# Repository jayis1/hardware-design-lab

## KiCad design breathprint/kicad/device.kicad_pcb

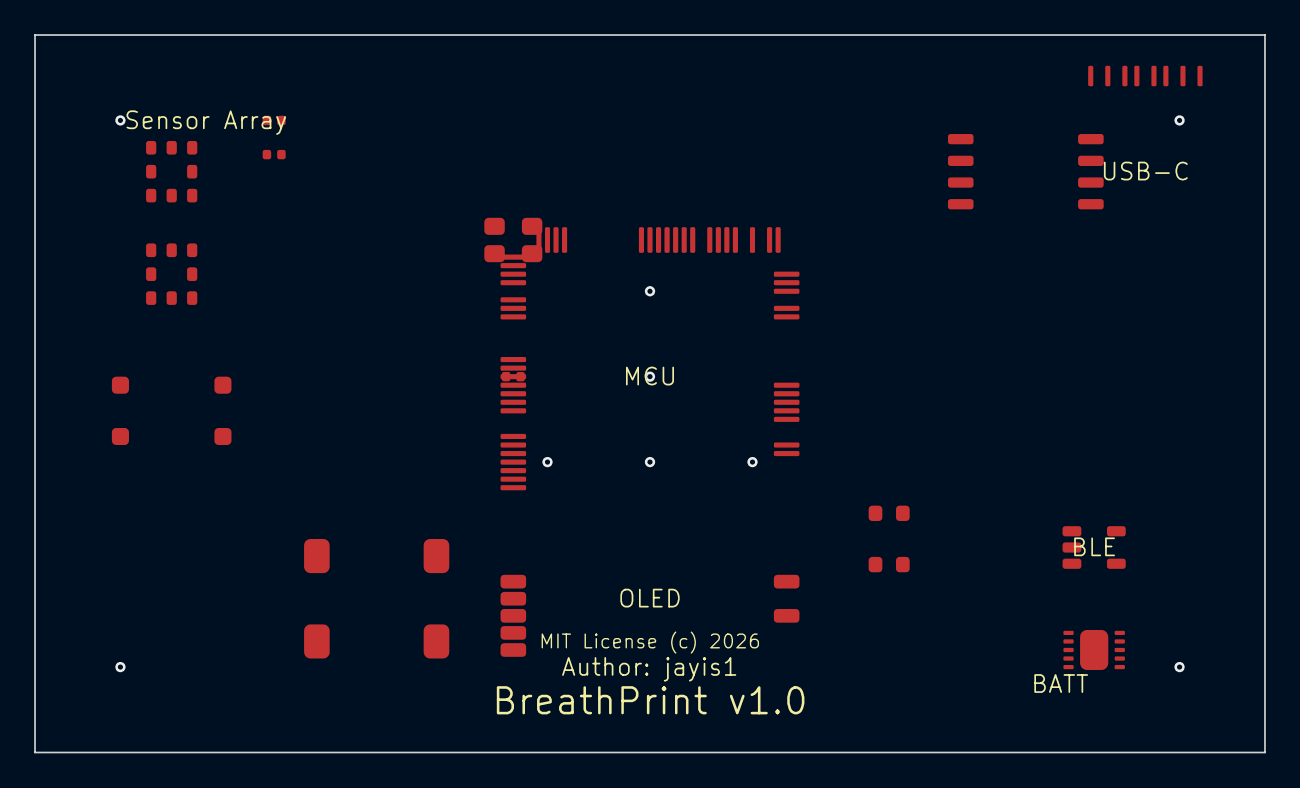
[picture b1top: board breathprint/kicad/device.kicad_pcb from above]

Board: 4 copper layers, 72.0 x 42.0 mm, 16 parts (0 on the bottom side), 23 nets, no tracks yet.

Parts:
C1: 100nF; C_0402_1005Metric
D1: Status_LED; LED_0603_1608Metric
D2: Sample_LED; LED_0603_1608Metric
J1: USB-C; USB_C_Receptacle_GCT_USB4085
R1, R2: 4.7k; R_0402_1005Metric
SW1: Analyze_BTN; SW_Push_1P1T_NO_6x6mm_H9.5mm
U1: STM32H733VGT6; LQFP-100_14x14mm_P0.5mm
U2, U3: BME688; Bosch_LCC-8_3.6x4.2mm_P1.2mm
U4: SCD41; Sensirion_SCD41
U5: W25Q64JVSIQ; SOIC-8_5.27x5.27mm_P1.27mm
U6: MCP73831T-2ACI; SOT-23-5
U7: TPS63031DSKR; VSON-10-1EP_3x3mm_P0.5mm_EP1.65x2.35mm
U8: SSD1306_128x64; SSD1306_0.96in_128x64
Y1: 16MHz; Crystal_SMD_3225-4Pin_3.2x2.5mm

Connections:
BTN_ANALYZE: SW1.1, SW1.3, U1.23
CHRG_STAT: U1.77, U6.1
DISP_CS: U1.51, U8.3
DISP_DC: U1.57, U8.4
DISP_RST: U1.56, U8.5
FLASH_CS: U1.3, U5.1
GND: C1.2, D1.2, D2.2, J1.A1, J1.B1, SW1.2, SW1.4, U1.10, U1.21, U1.27, U1.49, U1.74, U1.99, U2.2, U2.6, U2.7, U3.2, U3.7, U4.2, U5.4, U6.2, U6.5, U7.3, U7.4, U7.7, U7.8, U7.11, U8.2, Y1.2, Y1.4
HSE_IN: U1.12, Y1.1
HSE_OUT: U1.13, Y1.3
I2C1_SCL: R1.2, U1.92, U2.4, U3.4, U4.3
I2C1_SDA: R2.2, U1.93, U2.5, U3.5, U4.4
SAMPLE_LED: D2.1, U1.47
SPI2_MOSI: U1.54, U8.7
SPI2_SCK: U1.52, U8.6
SPI4_MISO: U1.4, U5.2
SPI4_MOSI: U1.1, U5.5
SPI4_SCK: U1.5, U5.6
STATUS_LED: D1.1, U1.46
USB_DM: J1.A7, U1.44
USB_DP: J1.A6, U1.45
VBAT: U1.6, U6.3, U7.1, U7.2
VCC: C1.1, R1.1, R2.1, U1.11, U1.22, U1.28, U1.50, U1.75, U1.100, U2.1, U2.3, U2.8, U3.1, U3.3, U3.6, U3.8, U4.1, U5.3, U5.7, U5.8, U7.5, U7.6, U7.9, U7.10, U8.1
VUSB: J1.A4, J1.B4, U6.4

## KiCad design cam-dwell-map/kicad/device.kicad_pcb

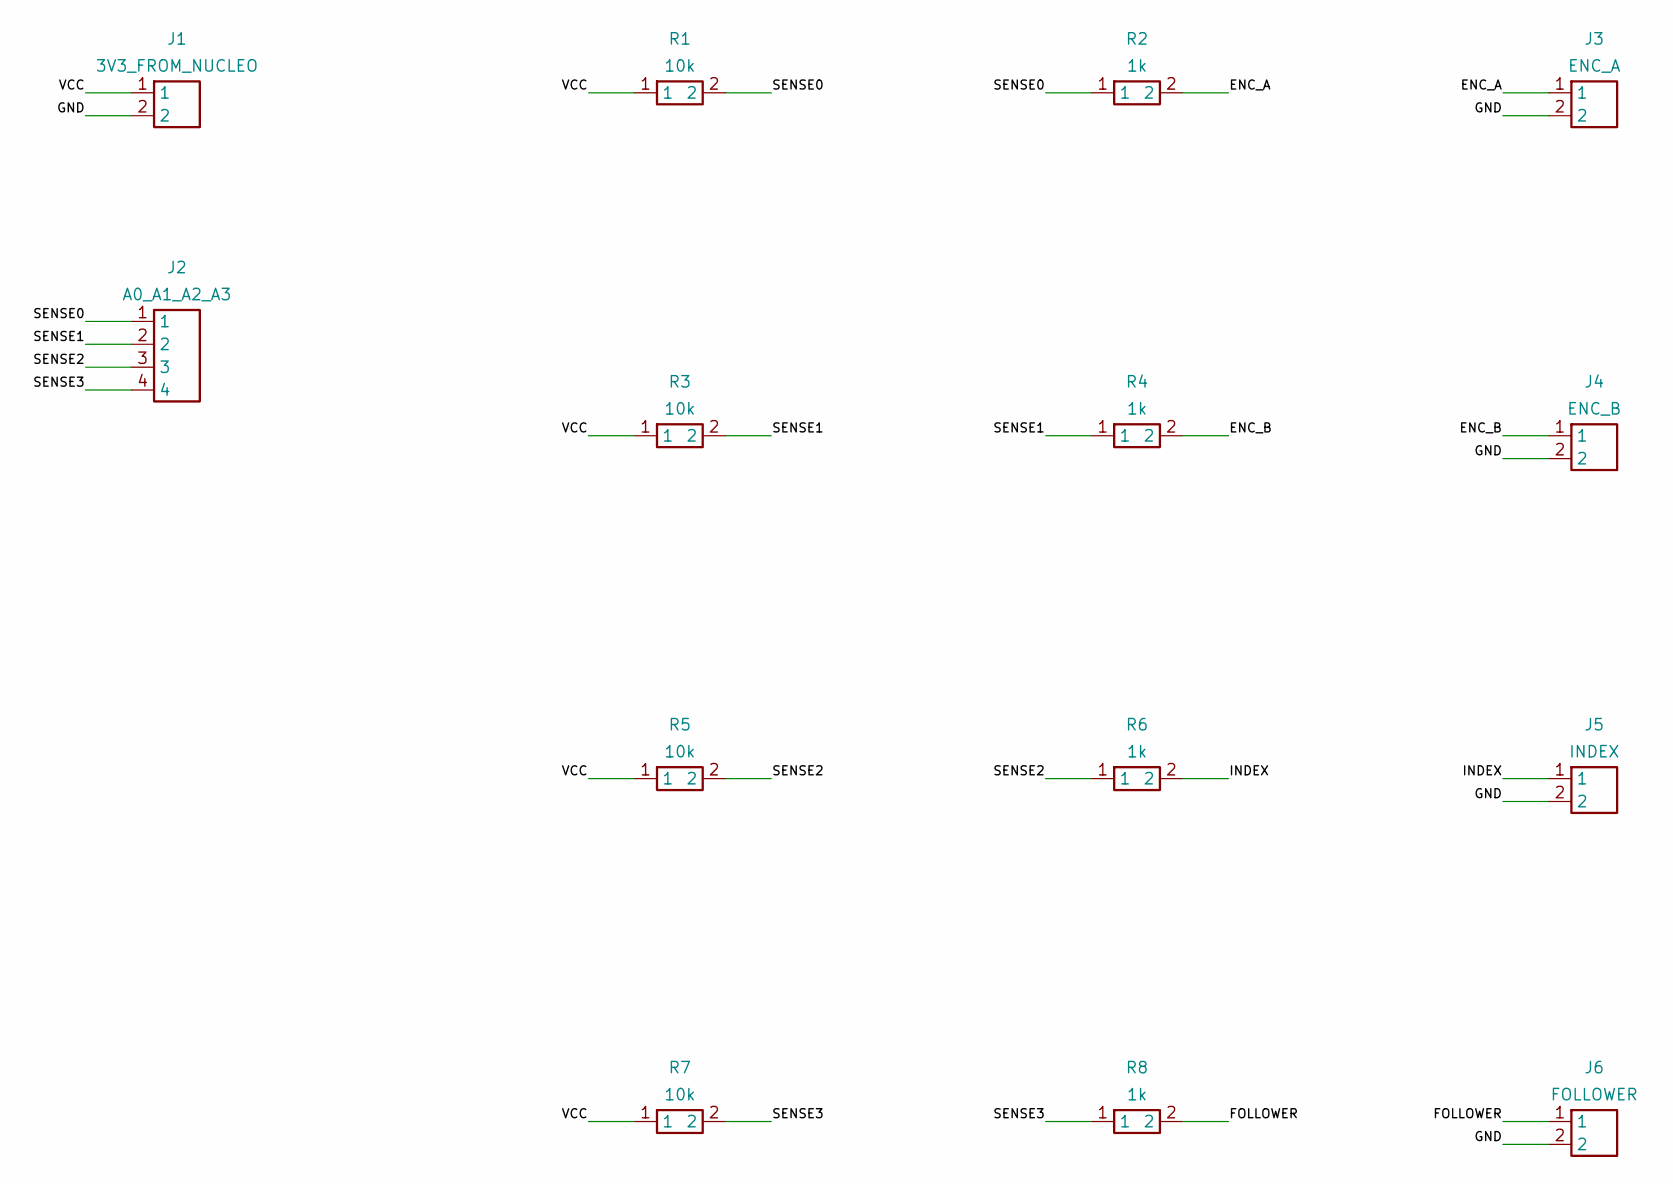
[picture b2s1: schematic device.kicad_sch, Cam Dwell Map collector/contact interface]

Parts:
J1: 3V3_FROM_NUCLEO; PinHeader_1x02_P2.54mm_Vertical
J2: A0_A1_A2_A3; PinHeader_1x04_P2.54mm_Vertical
J3: ENC_A; PinHeader_1x02_P2.54mm_Vertical
J4: ENC_B; PinHeader_1x02_P2.54mm_Vertical
J5: INDEX; PinHeader_1x02_P2.54mm_Vertical
J6: FOLLOWER; PinHeader_1x02_P2.54mm_Vertical
R1, R3, R5, R7: 10k; R_Axial_DIN0207_L6.3mm_D2.5mm_P7.62mm_Horizontal
R2, R4, R6, R8: 1k; R_Axial_DIN0207_L6.3mm_D2.5mm_P7.62mm_Horizontal

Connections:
ENC_A: J3.1, R2.2
ENC_B: J4.1, R4.2
FOLLOWER: J6.1, R8.2
GND: J1.2, J3.2, J4.2, J5.2, J6.2
INDEX: J5.1, R6.2
SENSE0: J2.1, R1.2, R2.1
SENSE1: J2.2, R3.2, R4.1
SENSE2: J2.3, R5.2, R6.1
SENSE3: J2.4, R7.2, R8.1
VCC: J1.1, R1.1, R3.1, R5.1, R7.1

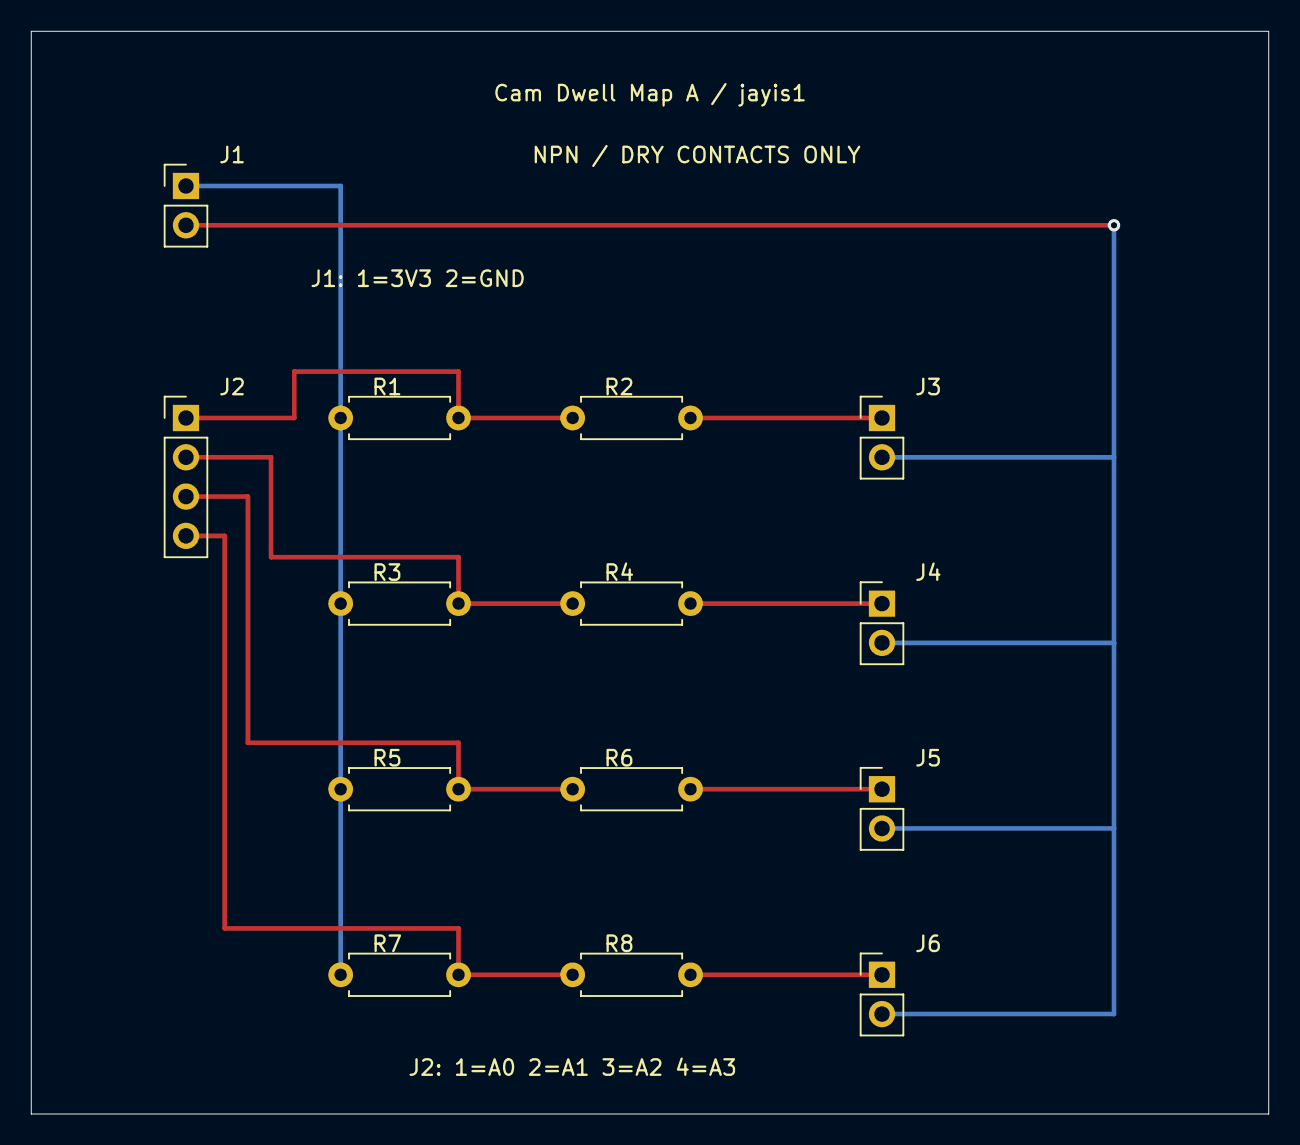
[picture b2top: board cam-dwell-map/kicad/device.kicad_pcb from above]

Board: 2 copper layers, 80.0 x 70.0 mm, 14 parts (0 on the bottom side), 10 nets.

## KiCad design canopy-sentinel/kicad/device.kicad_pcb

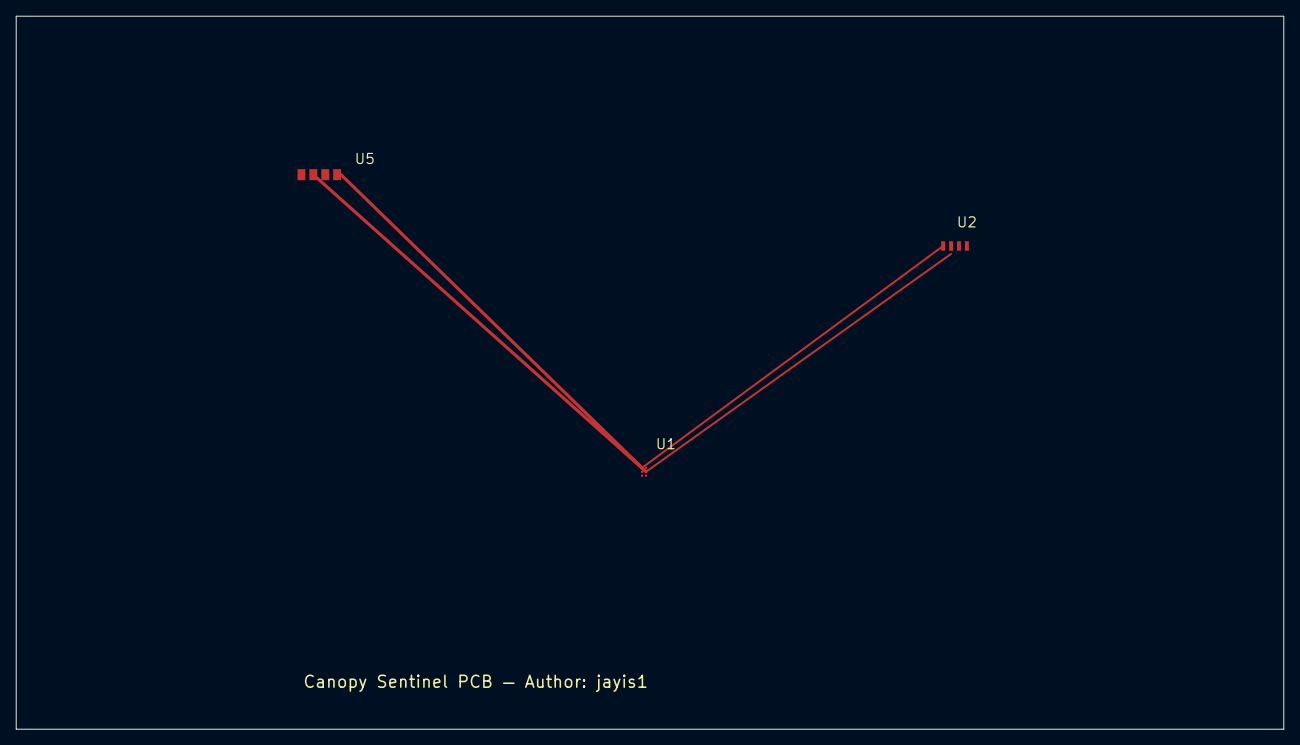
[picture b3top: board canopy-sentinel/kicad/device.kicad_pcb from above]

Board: 2 copper layers, 160.0 x 90.0 mm, 3 parts (0 on the bottom side), 4 nets.

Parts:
U1: STM32U585AII6; TFBGA-169_7x7mm_Layout13x13_P0.5mm
U2: MLX90640; LGA-32_8x8mm_P0.8mm
U5: ESP32-S3-WROOM-1

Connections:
3V3: U1.A1, U2.1, U5.1
GND: U1.A2, U2.4, U5.2
I2C1_SCL: U1.B1, U2.2
I2C1_SDA: U1.B2, U2.3

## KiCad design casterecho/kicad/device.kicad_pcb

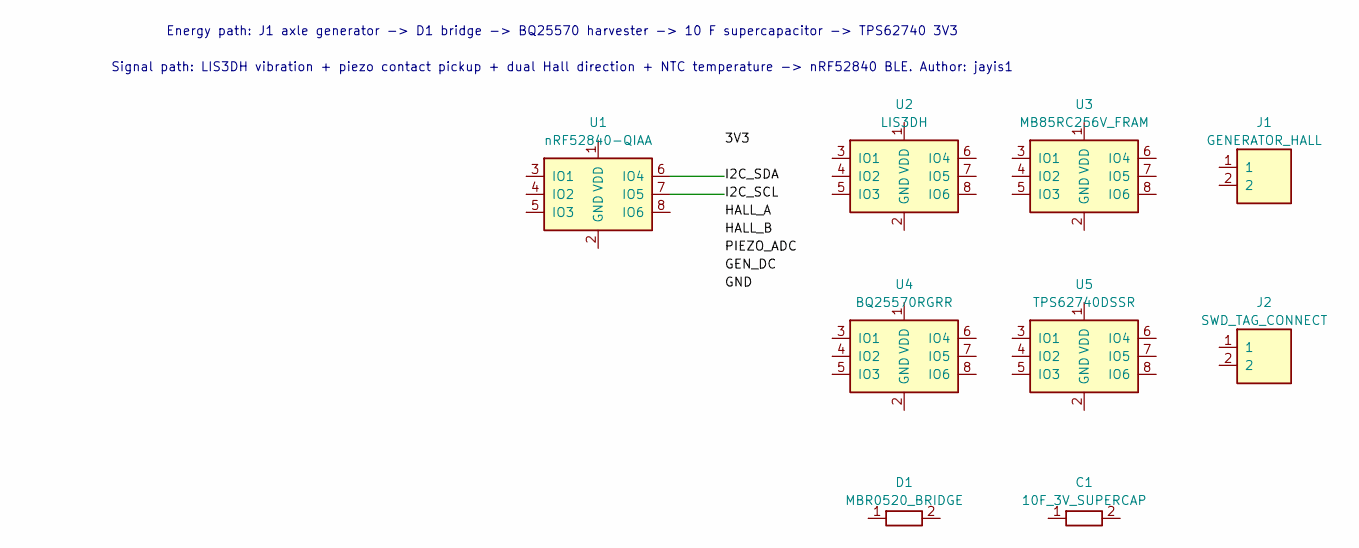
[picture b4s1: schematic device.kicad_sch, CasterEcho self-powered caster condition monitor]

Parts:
C1: 10F_3V_SUPERCAP; C_Radial_D12.5mm_H20.0mm_P5.00mm
D1: MBR0520_BRIDGE; D_SOD-123
J1: GENERATOR_HALL; JST_PH_S6B-PH-K_1x06_P2.00mm_Horizontal
J2: SWD_TAG_CONNECT; Tag-Connect_TC2030-IDC-NL_2x03_P1.27mm_Vertical
U1: nRF52840-QIAA; QFN-73-1EP_7x7mm_P0.4mm_EP5.2x5.2mm
U2: LIS3DH; LGA-16_3x3mm_P0.5mm
U3: MB85RC256V_FRAM; SOIC-8_3.9x4.9mm_P1.27mm
U4: BQ25570RGRR; VQFN-20-1EP_3.5x3.5mm_P0.5mm_EP2.2x2.2mm
U5: TPS62740DSSR; WSON-12-2x3mm_P0.5mm

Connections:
3V3: J1.6, J2.1, U1.1 (VDD), U2.1 (VDD), U3.1 (VDD), U5.3 (IO1)
BUCK_IN: D1.2, U4.4 (IO2), U5.1 (VDD)
GEN_DC: D1.1, J1.1, U4.1 (VDD)
GND: C1.2, J1.2, J2.3, U1.2 (GND), U1.73, U2.2 (GND), U3.2 (GND), U4.2 (GND), U4.21, U5.2 (GND)
HALL_A: J1.3, U1.5 (IO3)
HALL_B: J1.4, U1.6 (IO4)
I2C_SCL: U1.4 (IO2), U2.4 (IO2), U3.4 (IO2)
I2C_SDA: U1.3 (IO1), U2.3 (IO1), U3.3 (IO1)
IMU_INT: U1.10, U2.5 (IO3)
PIEZO_ADC: J1.5, U1.7 (IO5)
SUPERCAP: C1.1, U4.3 (IO1)
SWCLK: J2.4, U1.9
SWDIO: J2.2, U1.8 (IO6)

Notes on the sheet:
Energy path: J1 axle generator -> D1 bridge -> BQ25570 harvester -> 10 F supercapacitor -> TPS62740 3V3
Signal path: LIS3DH vibration + piezo contact pickup + dual Hall direction + NTC temperature -> nRF52840 BLE. Author: jayis1

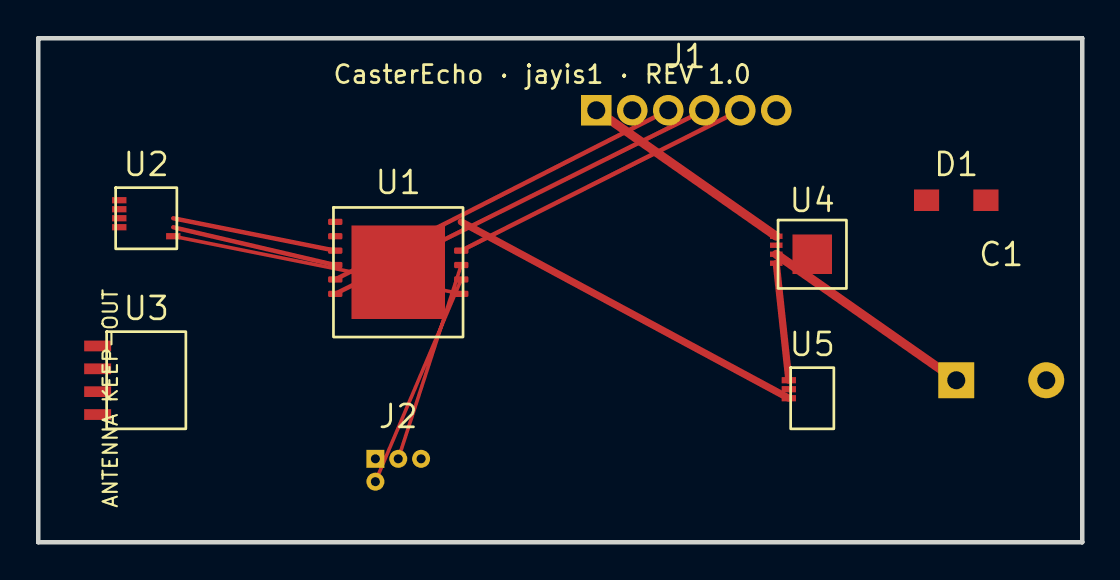
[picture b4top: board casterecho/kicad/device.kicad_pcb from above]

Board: 4 copper layers, 58.0 x 28.0 mm, 9 parts (0 on the bottom side), 13 nets.

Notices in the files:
breathprint/kicad/device.kicad_pcb:
MIT License (c) 2026
breathprint/kicad/device.kicad_sch:
MIT License — Copyright (c) 2026 jayis1
canopy-sentinel/kicad/device.kicad_sch:
License: CERN-OHL-S v2
chlormap/kicad/device.kicad_sch:
Copyright (C) 2026 jayis1. All rights reserved.
